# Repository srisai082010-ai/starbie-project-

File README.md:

# starbie-project-
This project is about building like a desktop Tamagotchi that was like very popular back in the 1980s where there's like display on stand or something and I am building the same thing but a star version 

Here is kicad file in which i am going to do the design and all of the building stuff in here and will be updating here every week 

Here is the photo:

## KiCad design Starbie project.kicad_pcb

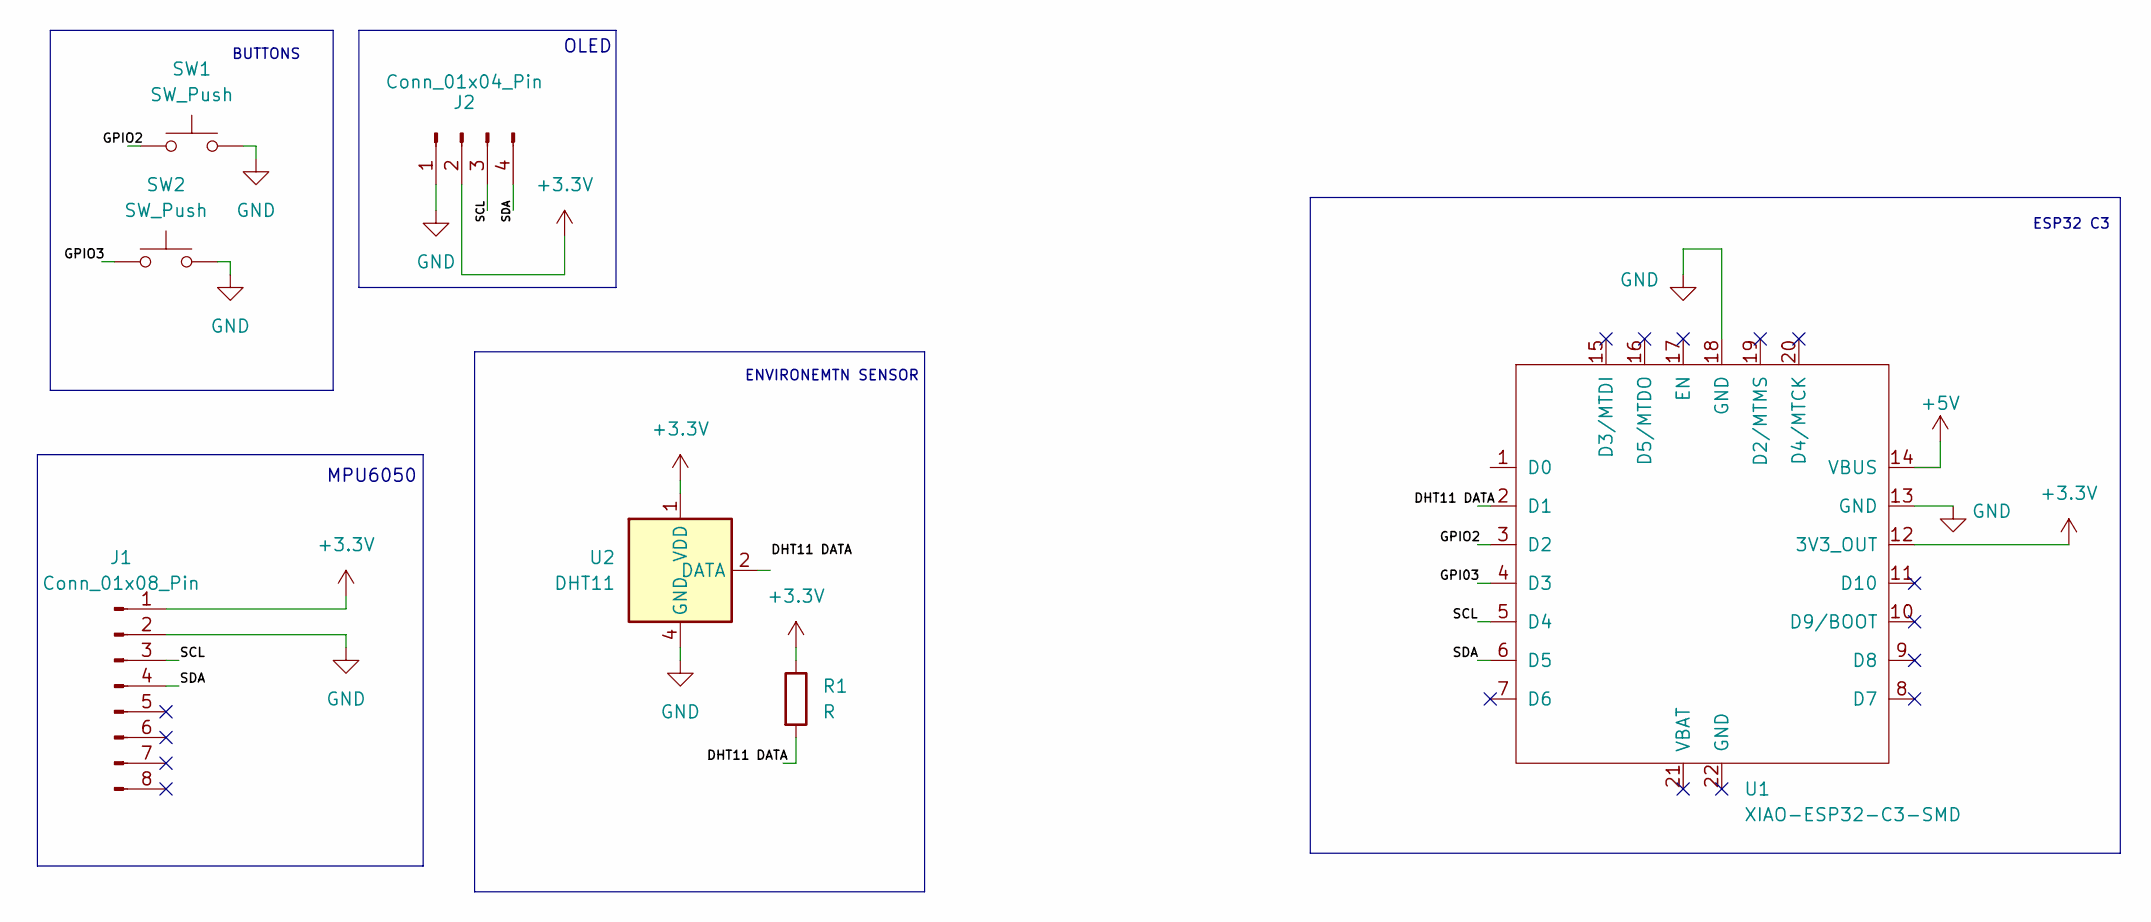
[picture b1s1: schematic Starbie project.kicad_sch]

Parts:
J1: Conn_01x08_Pin; MPU6050_Module
J2: Conn_01x04_Pin; Display_128x64_096_I2C
R1: R; R_Axial_DIN0207_L6.3mm_D2.5mm_P10.16mm_Horizontal
SW1, SW2: SW_Push; SW_PUSH_6mm_H5mm
U1: XIAO-ESP32-C3-SMD
U2: DHT11; Aosong_DHT11_5.5x12.0_P2.54mm

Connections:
+3.3V: J1.1, J2.2, R1.1, U1.12 (3V3_OUT), U2.1 (VDD)
+5V: U1.14 (VBUS)
/SCL: J1.3
/SDA: J1.4
GND: J1.2, J2.1, SW1.2 (2_2), SW2.2 (2_2), U1.13 (GND), U1.18 (GND), U2.4 (GND)

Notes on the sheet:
OLED
ENVIRONEMTN SENSOR
ESP32 C3
BUTTONS
MPU6050

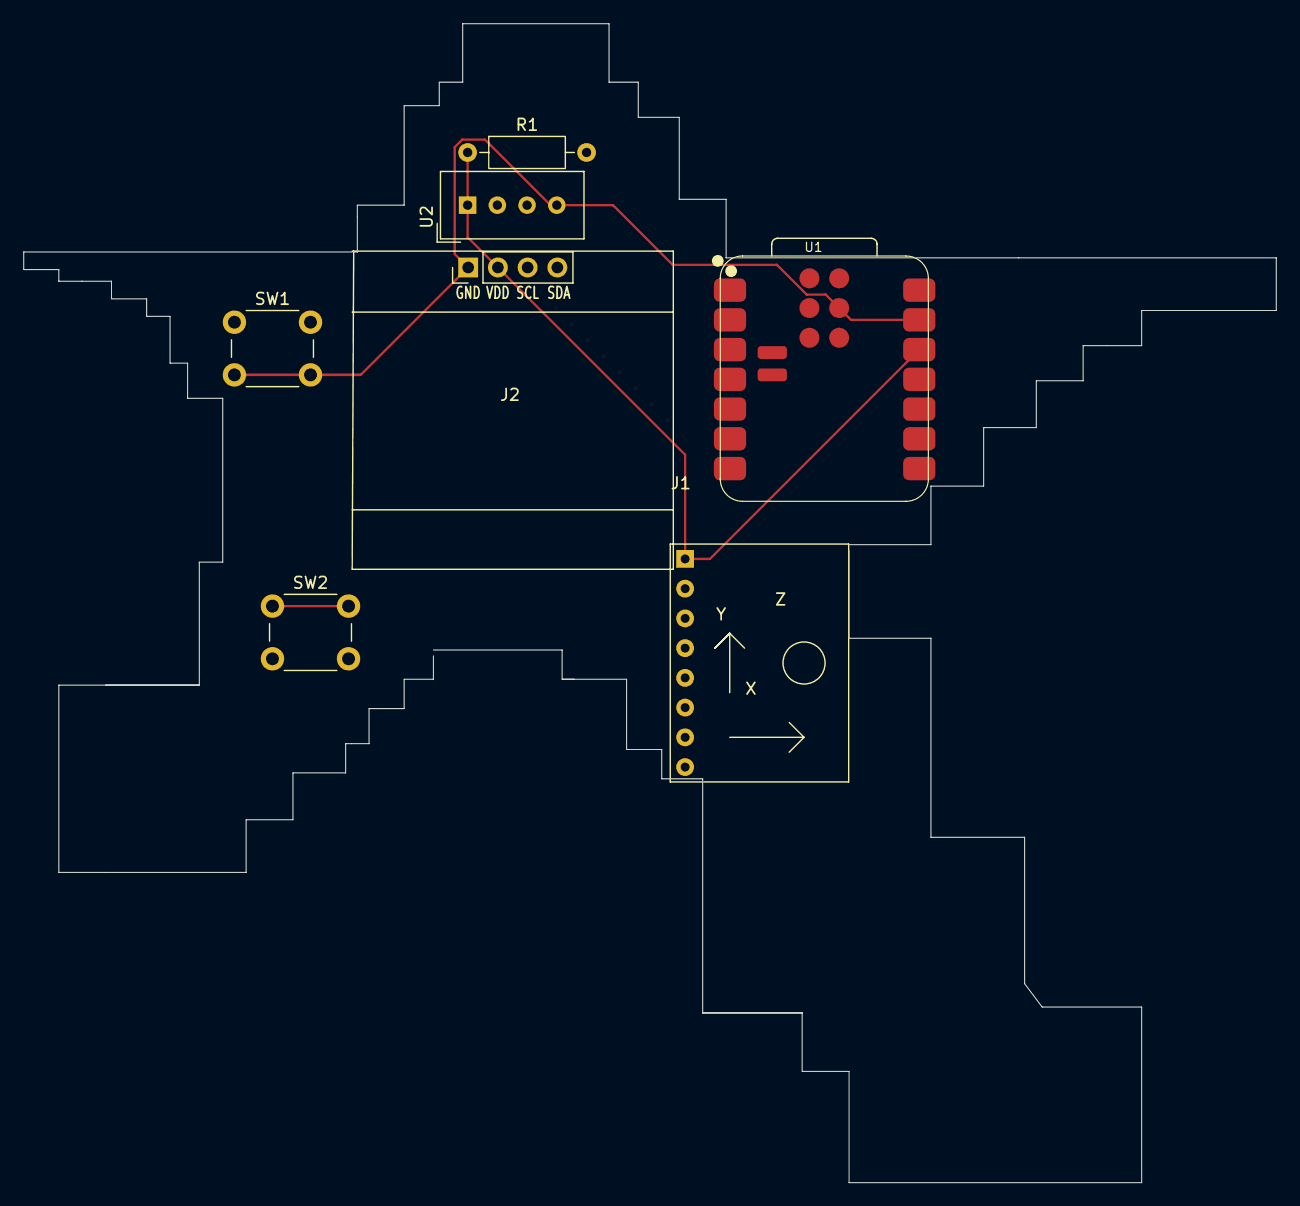
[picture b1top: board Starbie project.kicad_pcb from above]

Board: 2 copper layers, 107.0 x 99.0 mm, 7 parts (0 on the bottom side), 2 nets.
